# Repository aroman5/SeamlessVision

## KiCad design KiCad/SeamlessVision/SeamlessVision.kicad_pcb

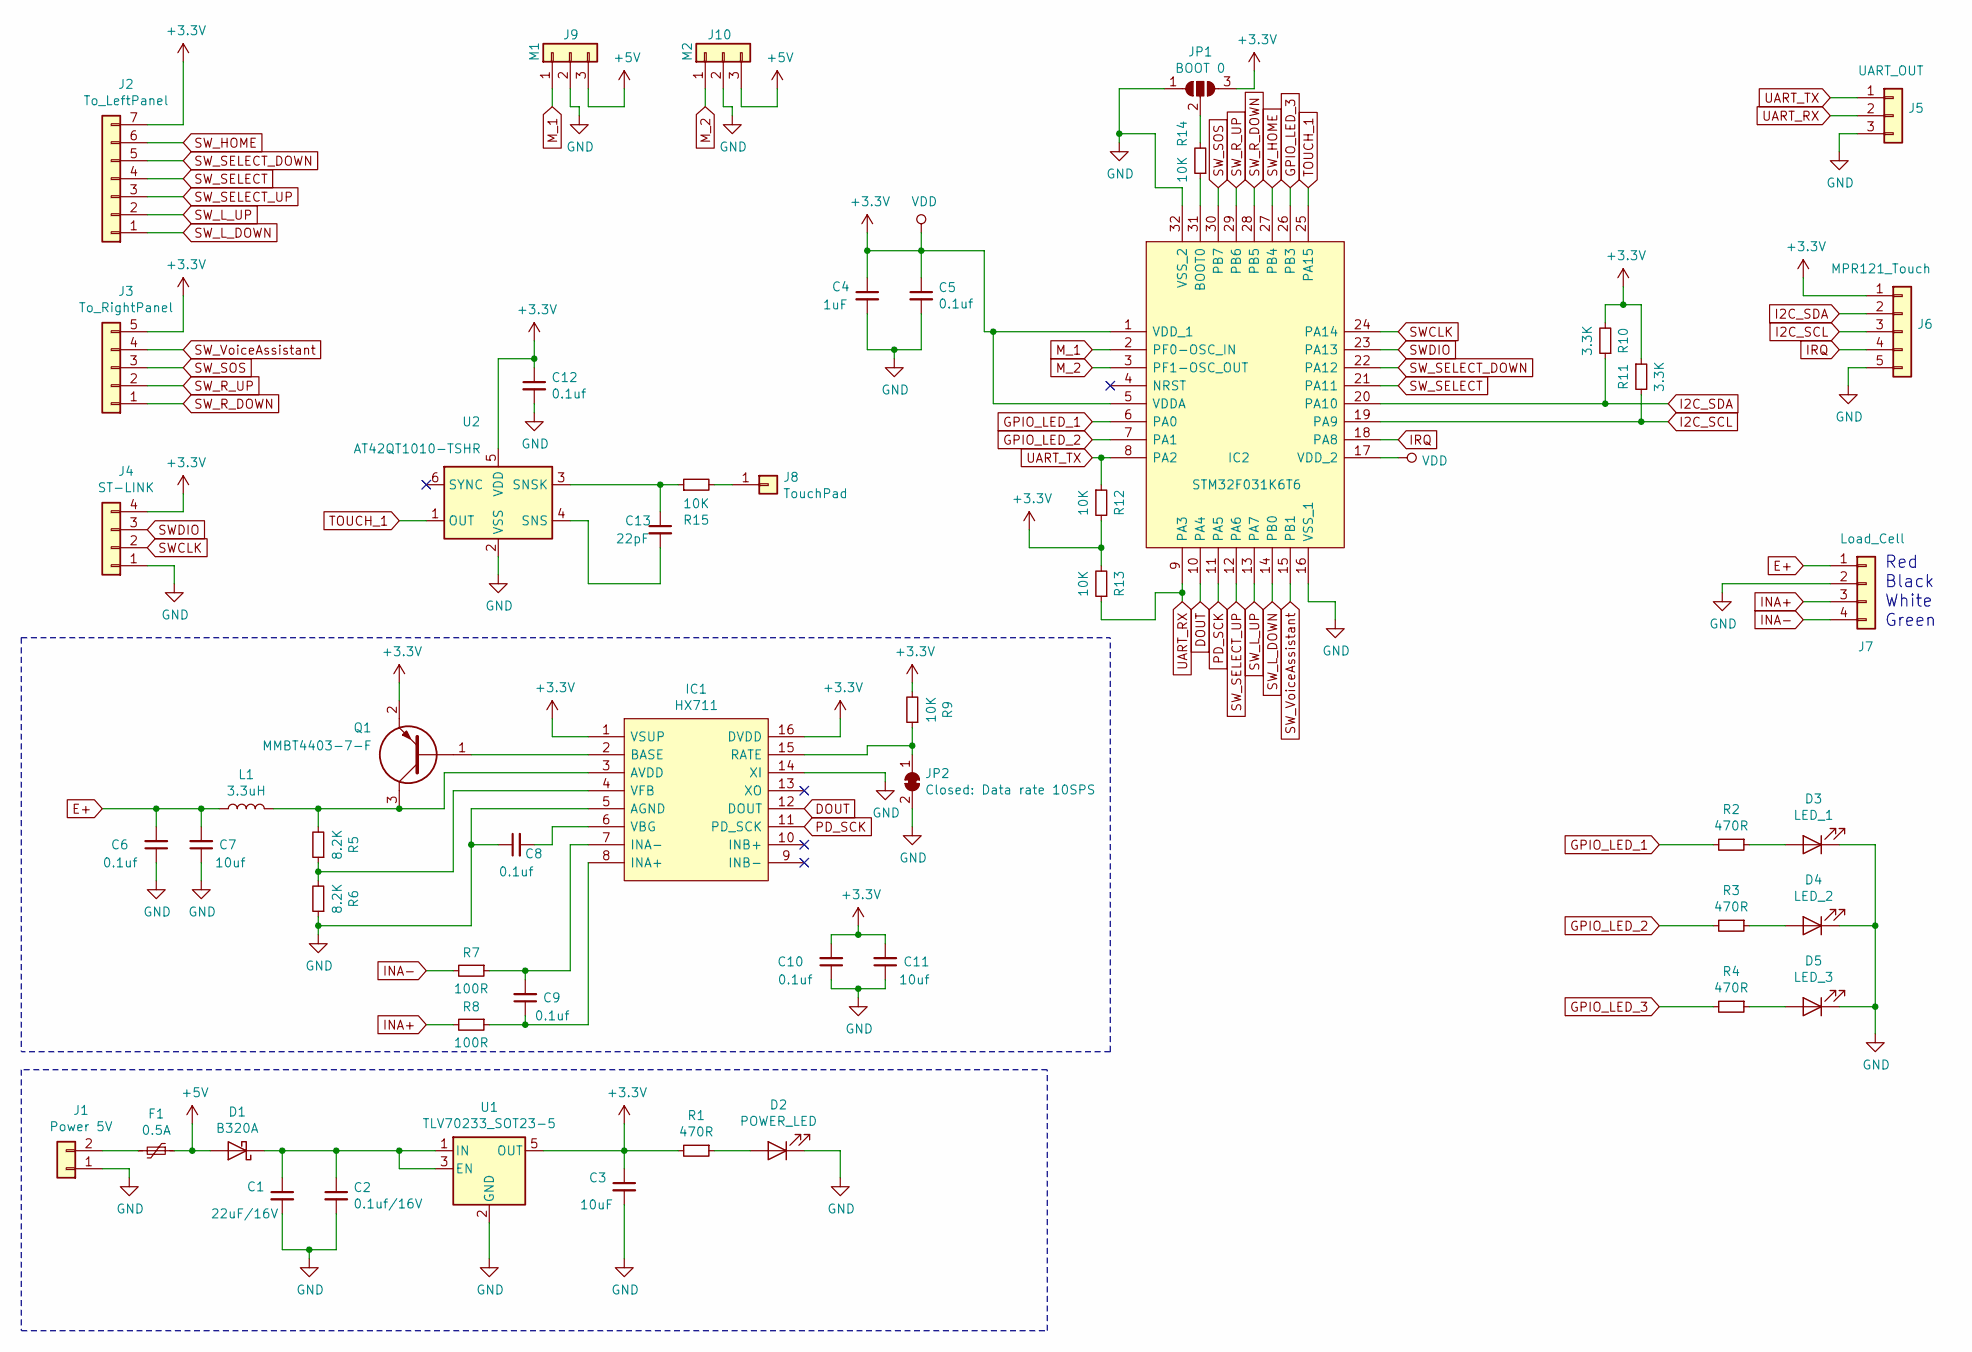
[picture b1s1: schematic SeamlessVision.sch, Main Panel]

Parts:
C1: 22uF/16V; C_1210_3225Metric
C2: 0.1uf/16V; C_0805_2012Metric
C3: 10uF; C_0805_2012Metric
C4: 1uF; C_0805_2012Metric
C5, C6, C8, C9, C10, C12: 0.1uf; C_0805_2012Metric
C7, C11: 10uf; C_0805_2012Metric
C13: 22pF; C_0805_2012Metric
D1: B320A; D_SMA
D2: POWER_LED; LED_0603_1608Metric
D3: LED_1; LED_0603_1608Metric
D4: LED_2; LED_0603_1608Metric
D5: LED_3; LED_0603_1608Metric
F1: 0.5A; FUSC3216X55N
IC1: HX711; SOIC127P600X160-16N; Manufacturer_Part_Number HX711
IC2: STM32F031K6T6; QFP80P900X900X160-32N; Mouser Part Number 511-STM32F031K6T6
J1: Power 5V; JST_PH_B2B-PH-SM4-TB_02x2.00mm_Straight
J2: To_LeftPanel; Molex_PicoBlade_53261-0771_1x07-1MP_P1.25mm_Horizontal
J3: To_RightPanel; Molex_PicoBlade_53261-0571_1x05-1MP_P1.25mm_Horizontal
J4: ST-LINK; Molex_PicoBlade_53398-0471_1x04-1MP_P1.25mm_Vertical
J5: UART_OUT; Molex_PicoBlade_53261-0371_1x03-1MP_P1.25mm_Horizontal
J6: MPR121_Touch; Molex_PicoBlade_53261-0571_1x05-1MP_P1.25mm_Horizontal
J7: Load_Cell; Molex_PicoBlade_53398-0471_1x04-1MP_P1.25mm_Vertical
J8: TouchPad; PinHeader_1x01_P2.54mm_Vertical
J9: M1; Molex_PicoBlade_53398-0371_1x03-1MP_P1.25mm_Vertical
J10: M2; Molex_PicoBlade_53398-0371_1x03-1MP_P1.25mm_Vertical
JP1: BOOT 0; SolderJumper-3_P1.3mm_Open_RoundedPad1.0x1.5mm
JP2: Closed: Data rate 10SPS; SolderJumper-2_P1.3mm_Bridged_RoundedPad1.0x1.5mm
L1: 3.3uH; L_1210
Q1: MMBT4403-7-F; SOT96P240X120-3N; Mouser Part Number 621-MMBT4403-F
R1, R2, R3, R4: 470R; R_0603_1608Metric
R5, R6: 8.2K; R_0603_1608Metric
R7, R8: 100R; R_0603_1608Metric
R9, R12, R13, R14, R15: 10K; R_0603_1608Metric
R10, R11: 3.3K; R_0603_1608Metric
U1: TLV70233_SOT23-5; SOT-23-5
U2: AT42QT1010-TSHR; SOT-23-6

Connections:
+3V3: C3.1, C4.1, C5.1, C10.2, C11.2, C12.1, IC1.1 (VSUP), IC1.16 (DVDD), IC2.1 (VDD_1), IC2.5 (VDDA), IC2.17 (VDD_2), J2.7, J3.5, J4.4, J6.1, JP1.3 (B), Q1.2, R1.2, R9.2, R10.2, R11.1, R12.2, R13.2, U1.5 (OUT), U2.5 (VDD); also elsewhere on the board
+5V: D1.2 (A), F1.1, J9.3, J10.3
DOUT: IC1.12 (DOUT), IC2.10 (PA4)
E+: C6.2, C7.2, J7.1, L1.1
GND: C1.2, C2.2, C3.2, C4.2, C5.2, C6.1, C7.1, C8.1, C10.1, C11.1, C12.2, D2.1 (K), D3.1 (K), D4.1 (K), D5.1 (K), IC1.5 (AGND), IC1.14 (XI), IC2.16 (VSS_1), IC2.32 (VSS_2), J1.1, J4.1, J5.3, J6.5, J7.2, J9.2, J10.2, JP1.1 (A), JP2.2 (B), R6.1, U1.2 (GND), U2.2 (VSS); also elsewhere on the board
GPIO_LED_1: IC2.6 (PA0), R2.2
GPIO_LED_2: IC2.7 (PA1), R3.2
GPIO_LED_3: IC2.26 (PB3), R4.2
I2C_SCL: IC2.19 (PA9), J6.3, R11.2
I2C_SDA: IC2.20 (PA10), J6.2, R10.1
INA+: J7.3, R8.2
INA-: J7.4, R7.2
IRQ: IC2.18 (PA8), J6.4
M_1: IC2.2 (PF0-OSC_IN), J9.1
M_2: IC2.3 (PF1-OSC_OUT), J10.1
unnamed: C1.1, C2.1, D1.1 (K), U1.1 (IN), U1.3 (EN)
unnamed: C8.2, IC1.6 (VBG)
unnamed: C9.1, IC1.8 (INA+), R8.1
unnamed: C9.2, IC1.7 (INA-), R7.1
unnamed: C13.1, R15.1, U2.3 (SNSK)
unnamed: C13.2, U2.4 (SNS)
unnamed: D2.2 (A), R1.1
unnamed: D3.2 (A), R2.1
unnamed: D4.2 (A), R3.1
unnamed: D5.2 (A), R4.1
unnamed: F1.2, J1.2
unnamed: IC1.2 (BASE), Q1.1
unnamed: IC1.3 (AVDD), L1.2, Q1.3, R5.2
unnamed: IC1.4 (VFB), R5.1, R6.2
unnamed: IC1.15 (RATE), JP2.1 (A), R9.1
unnamed: IC2.31 (BOOT0), R14.1
unnamed: J8.1, R15.2
unnamed 32: JP1.2 (C), R14.2; also elsewhere on the board
PD_SCK: IC1.11 (PD_SCK), IC2.11 (PA5)
SWCLK: IC2.24 (PA14), J4.2
SWDIO: IC2.23 (PA13), J4.3
SW_HOME: IC2.27 (PB4), J2.6
SW_L_DOWN: IC2.14 (PB0), J2.1
SW_L_UP: IC2.13 (PA7), J2.2
SW_R_DOWN: IC2.28 (PB5), J3.1
SW_R_UP: IC2.29 (PB6), J3.2
SW_SELECT: IC2.21 (PA11), J2.4
SW_SELECT_DOWN: IC2.22 (PA12), J2.5
SW_SELECT_UP: IC2.12 (PA6), J2.3
SW_SOS: IC2.30 (PB7), J3.3
SW_VoiceAssistant: IC2.15 (PB1), J3.4
TOUCH_1: IC2.25 (PA15), U2.1 (OUT)
UART_RX: IC2.9 (PA3), J5.2, R13.1
UART_TX: IC2.8 (PA2), J5.1, R12.1

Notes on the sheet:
Red Black White Green

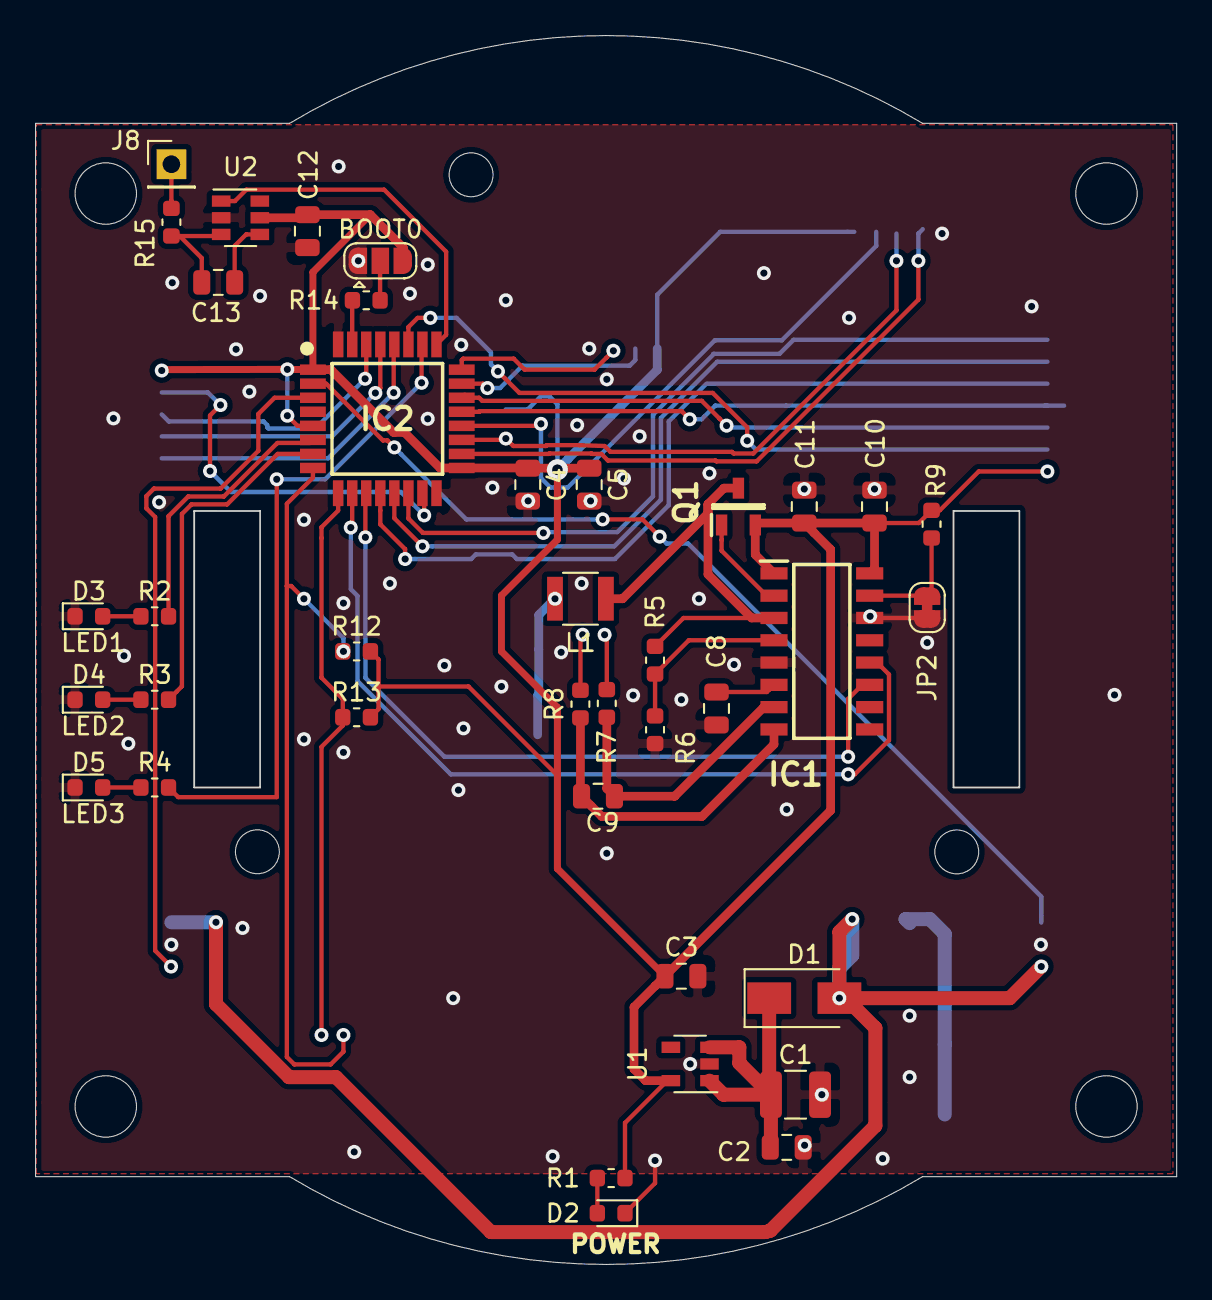
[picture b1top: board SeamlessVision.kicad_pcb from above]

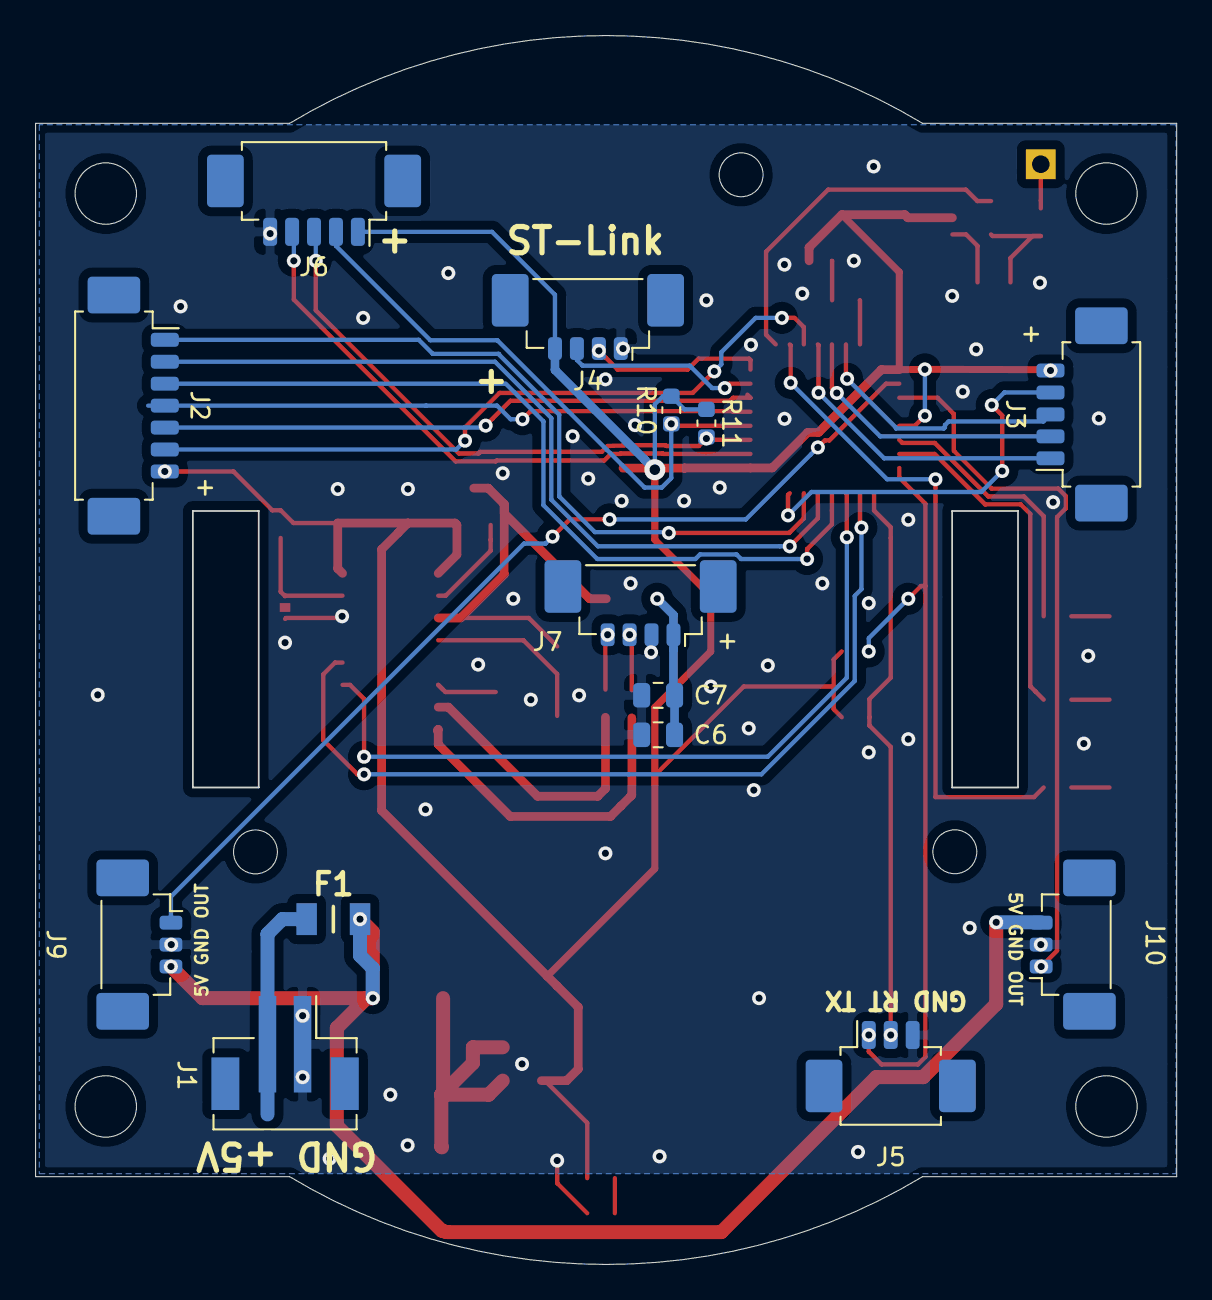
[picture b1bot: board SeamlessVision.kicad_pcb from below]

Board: 2 copper layers, 65.0 x 70.0 mm, 52 parts (14 on the bottom side), 49 nets.

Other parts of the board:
BOOT0: BOOT 0; SolderJumper-3_P1.3mm_Open_RoundedPad1.0x1.5mm

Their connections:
+3V3: BOOT0.3; also elsewhere on the board
GND: BOOT0.1; also elsewhere on the board
unnamed 32: BOOT0.2; also elsewhere on the board

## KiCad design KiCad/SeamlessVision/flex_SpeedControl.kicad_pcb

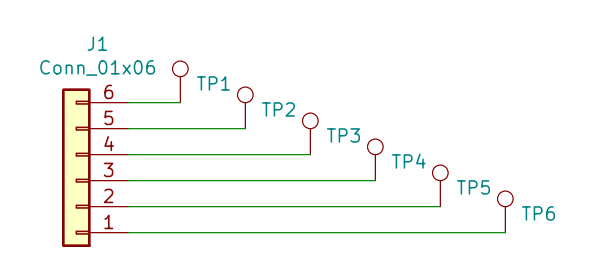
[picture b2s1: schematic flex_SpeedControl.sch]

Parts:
J1: Conn_01x06; PinHeader_2x03_P2.00mm_Vertical_SMD
TP1, TP2, TP3, TP4, TP5, TP6: TestPoint; TestPoint_Pad_D1.0mm

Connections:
unnamed: J1.1, TP6.1
unnamed: J1.2, TP5.1
unnamed: J1.3, TP4.1
unnamed: J1.4, TP3.1
unnamed: J1.5, TP2.1
unnamed: J1.6, TP1.1

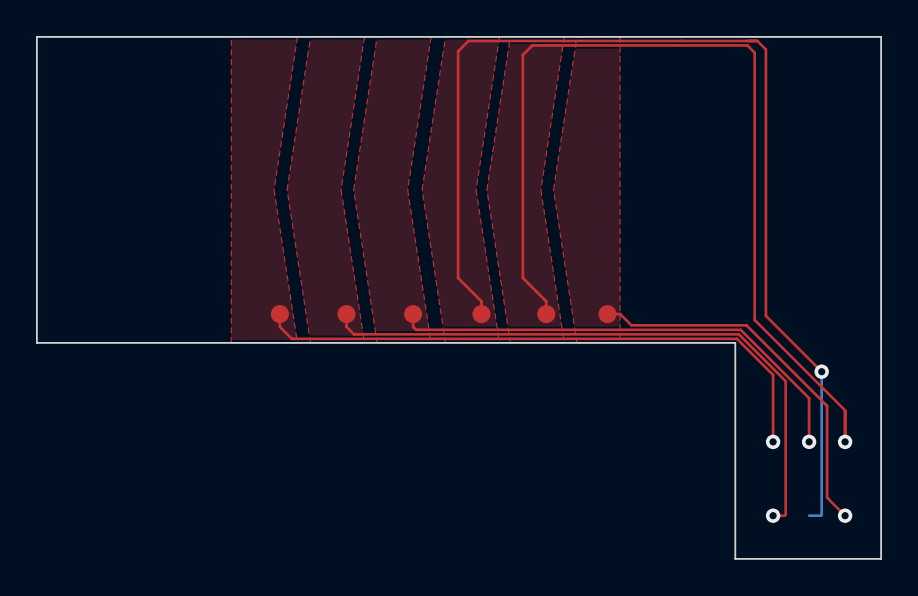
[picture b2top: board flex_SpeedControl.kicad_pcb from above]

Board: 2 copper layers, 46.9 x 29.0 mm, 7 parts (1 on the bottom side), 6 nets.

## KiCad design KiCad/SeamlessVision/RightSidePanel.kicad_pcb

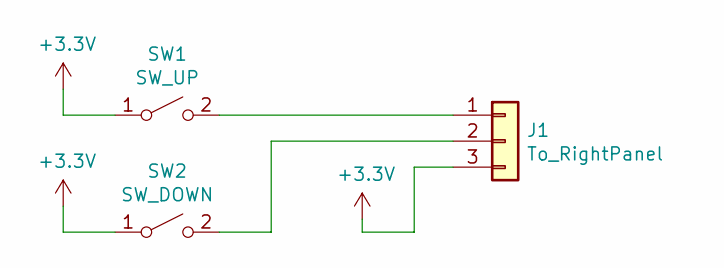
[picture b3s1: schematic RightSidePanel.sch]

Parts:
J1: To_RightPanel; Molex_PicoBlade_53398-0371_1x03-1MP_P1.25mm_Vertical
SW1: SW_UP; B3FS4002P
SW2: SW_DOWN; B3FS4002P

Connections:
+3V3: J1.3, SW1.1 (A), SW2.1 (A)
unnamed: J1.1, SW1.2 (B)
unnamed: J1.2, SW2.2 (B)

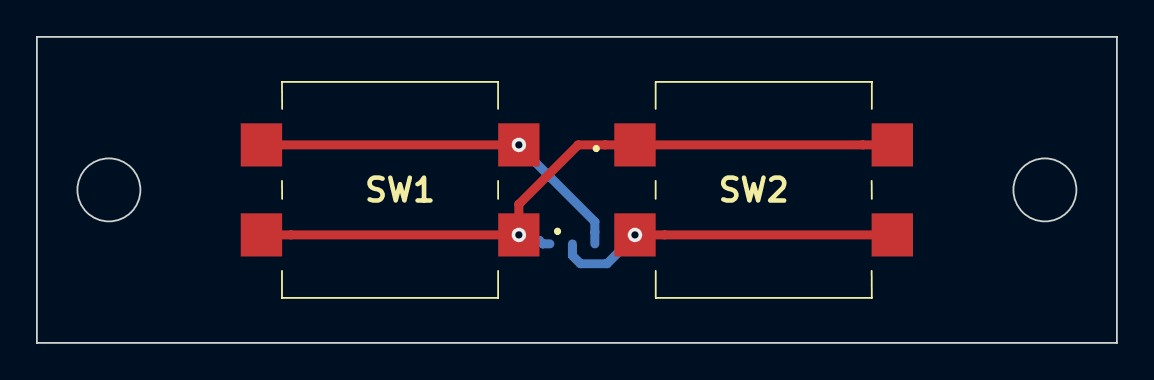
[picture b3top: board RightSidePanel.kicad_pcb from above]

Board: 2 copper layers, 60.0 x 17.0 mm, 3 parts (1 on the bottom side), 3 nets.

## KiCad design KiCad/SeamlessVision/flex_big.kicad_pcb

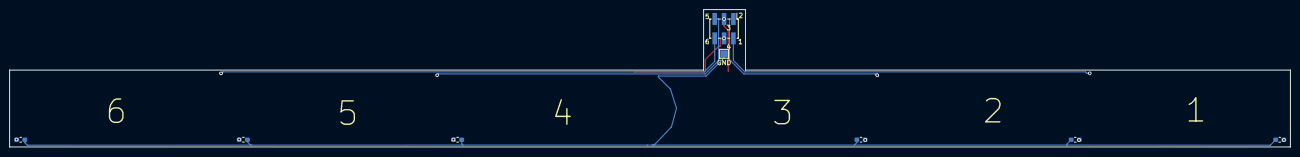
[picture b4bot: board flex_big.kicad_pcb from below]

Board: 2 copper layers, 275.0 x 29.5 mm, 8 parts (8 on the bottom side), 7 nets.

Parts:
C1, C2, C3, C4, C5, C6: 10pF; C_0603_1608Metric_Pad1.05x0.95mm_HandSolder
GND: Conn_01x07; TestPoint_Pad_1.5x1.5mm
J1: Conn_01x07; PinHeader_2x03_P2.00mm_Vertical_SMD

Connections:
GND: C1.2, C2.2, C3.2, C4.2, C5.2, C6.2, GND.1
unnamed: C1.1, J1.1
unnamed: C2.1, J1.2
unnamed: C3.1, J1.3
unnamed: C4.1, J1.4
unnamed: C5.1, J1.5
unnamed: C6.1, J1.6

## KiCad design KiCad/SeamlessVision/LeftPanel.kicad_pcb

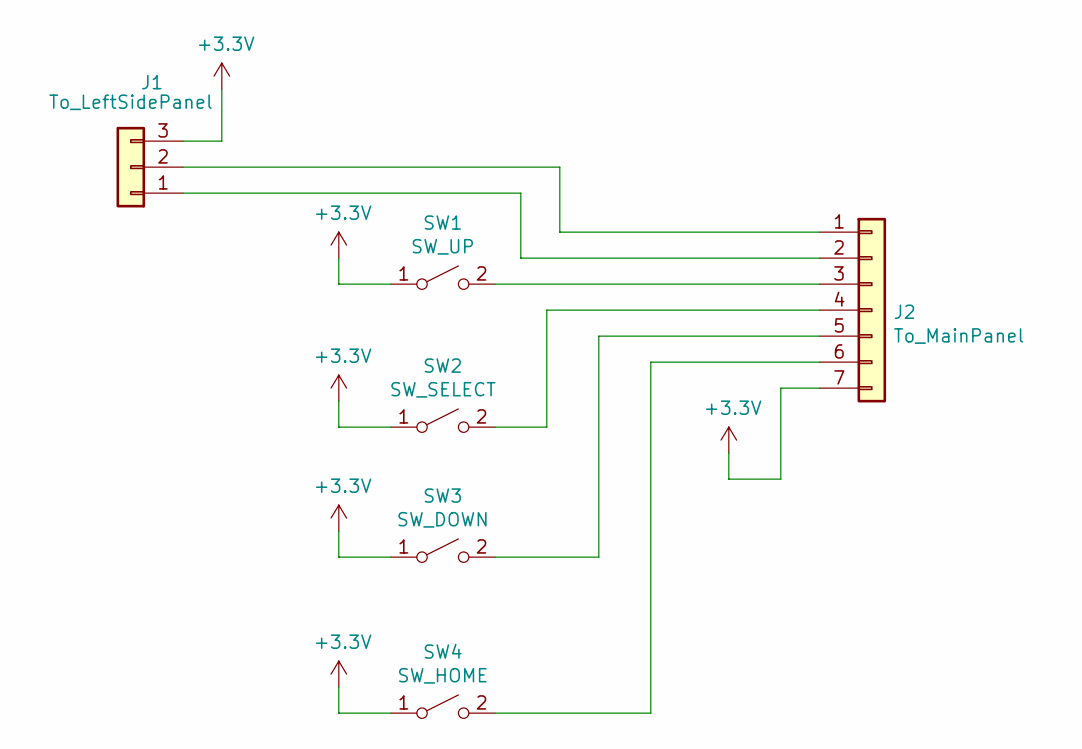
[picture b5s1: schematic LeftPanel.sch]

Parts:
J1: To_LeftSidePanel; Molex_PicoBlade_53261-0371_1x03-1MP_P1.25mm_Horizontal
J2: To_MainPanel; Molex_PicoBlade_53261-0771_1x07-1MP_P1.25mm_Horizontal
SW1: SW_UP; B3FS4002P
SW2: SW_SELECT; B3FS4002P
SW3: SW_DOWN; B3FS4002P
SW4: SW_HOME; B3FS4002P

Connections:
+3V3: J1.3, J2.7, SW1.1 (A), SW2.1 (A), SW3.1 (A), SW4.1 (A)
unnamed: J1.1, J2.2
unnamed: J1.2, J2.1
unnamed: J2.3, SW1.2 (B)
unnamed: J2.4, SW2.2 (B)
unnamed: J2.5, SW3.2 (B)
unnamed: J2.6, SW4.2 (B)

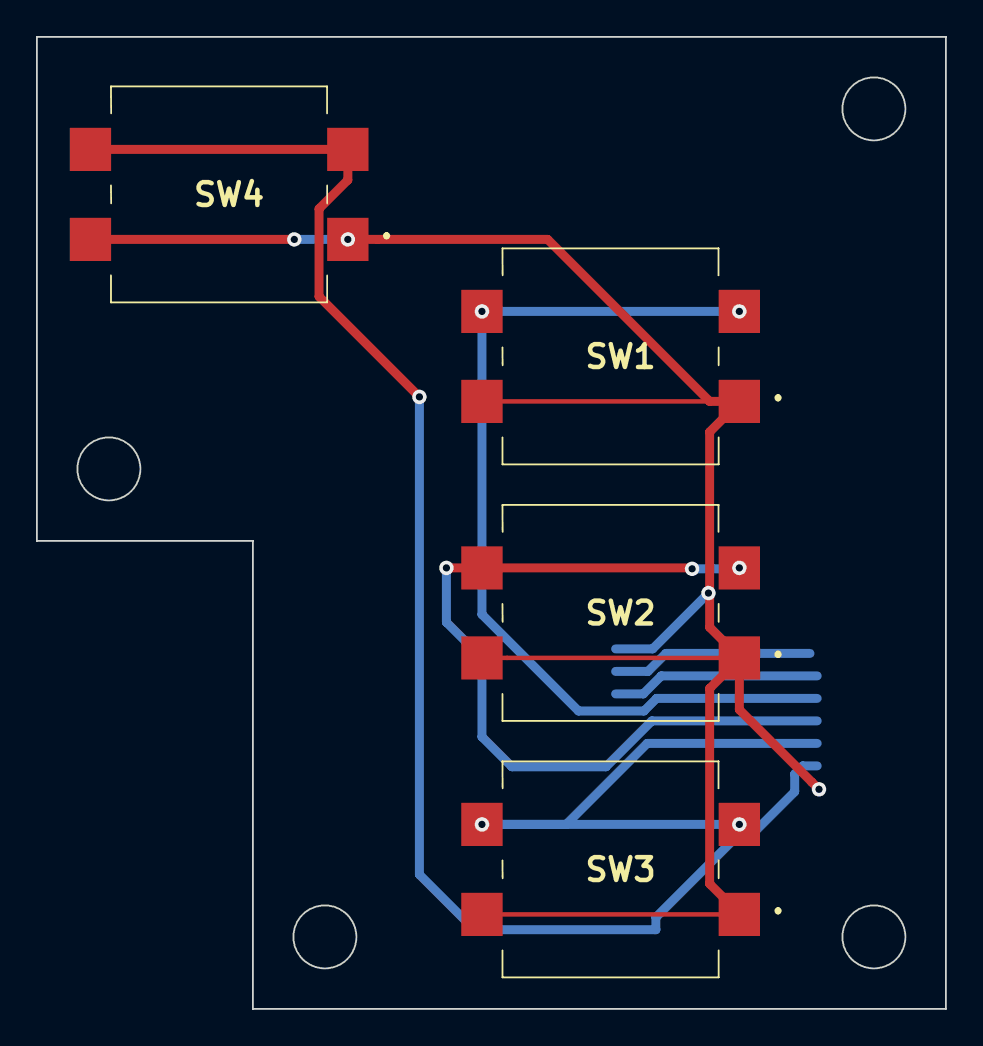
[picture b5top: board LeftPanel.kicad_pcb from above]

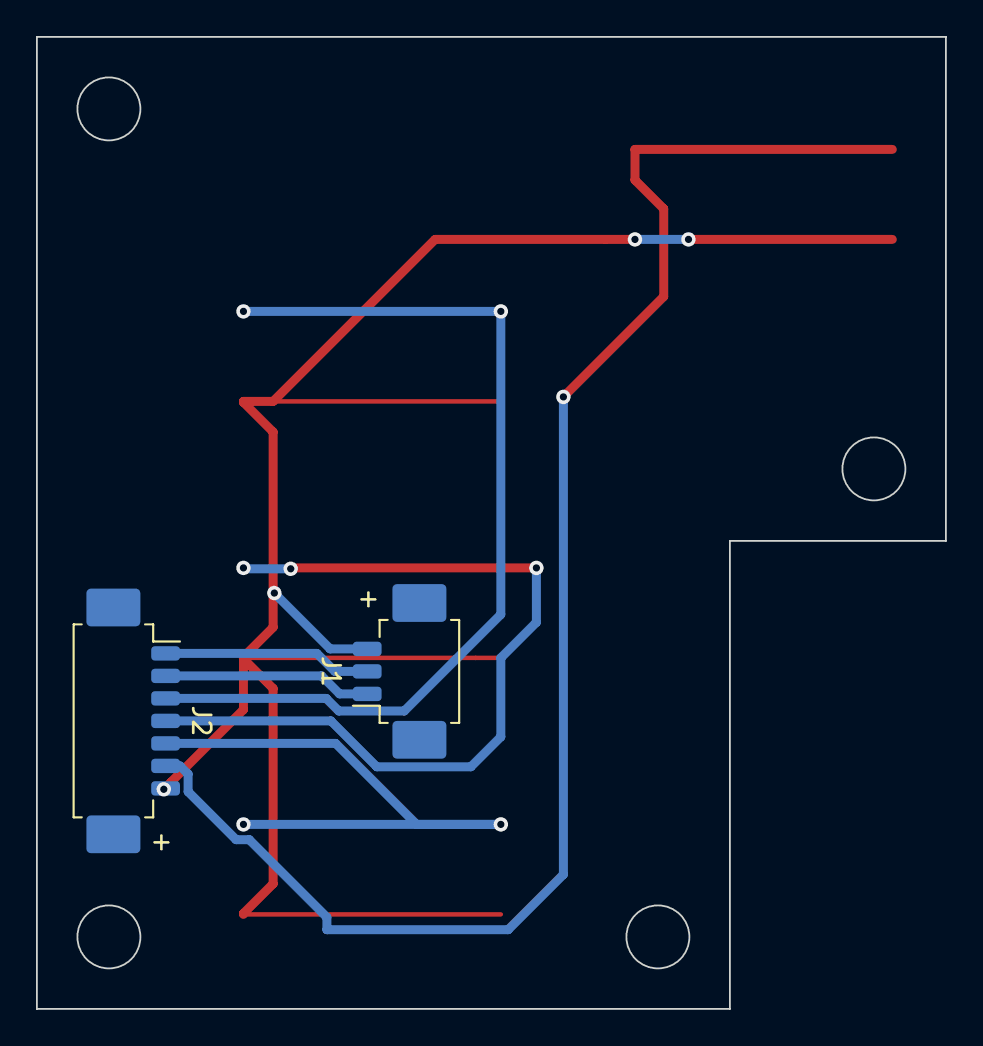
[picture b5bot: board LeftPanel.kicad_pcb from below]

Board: 2 copper layers, 50.5 x 54.0 mm, 6 parts (2 on the bottom side), 7 nets.

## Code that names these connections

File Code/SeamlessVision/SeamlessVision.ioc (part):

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Mcu.Name=STM32F031K6Tx
Mcu.Package=LQFP32
Mcu.UserName=STM32F031K6Tx
PA0.GPIOParameters=GPIO_Label
PA0.GPIO_Label=LED_1
PA0.Signal=GPIO_Output
PA1.GPIOParameters=GPIO_Label
PA1.GPIO_Label=LED_2
PA1.Signal=GPIO_Output
PA10.Mode=I2C
PA10.Signal=I2C1_SDA
PA11.GPIOParameters=GPIO_PuPd,GPIO_Label
PA11.GPIO_Label=SW_SELECT
PA11.GPIO_PuPd=GPIO_PULLDOWN
PA11.Signal=GPIO_Input
PA12.GPIOParameters=GPIO_PuPd,GPIO_Label
PA12.GPIO_Label=SW_SELECT_DOWN
PA12.GPIO_PuPd=GPIO_PULLDOWN
PA12.Signal=GPIO_Input
PA13.Mode=Serial_Wire
PA13.Signal=SYS_SWDIO
PA14.Mode=Serial_Wire
PA14.Signal=SYS_SWCLK
PA15.GPIOParameters=GPIO_PuPd,GPIO_Label
PA15.GPIO_Label=TOUCH_1
PA15.GPIO_PuPd=GPIO_NOPULL
PA15.Signal=GPIO_Input
PA2.Mode=Asynchronous
PA2.Signal=USART1_TX
PA3.Mode=Asynchronous
PA3.Signal=USART1_RX
PA4.GPIOParameters=GPIO_PuPd,GPIO_Label
PA4.GPIO_Label=HX711OUTPUT
PA4.GPIO_PuPd=GPIO_PULLDOWN
PA4.Signal=GPIO_Input
PA5.GPIOParameters=GPIO_PuPd,GPIO_Label
PA5.GPIO_Label=HX711SCK
PA5.GPIO_PuPd=GPIO_NOPULL
PA5.Signal=GPIO_Output
PA6.GPIOParameters=GPIO_PuPd,GPIO_Label
PA6.GPIO_Label=SW_SELECT_UP
PA6.GPIO_PuPd=GPIO_PULLDOWN
PA6.Signal=GPIO_Input
PA7.GPIOParameters=GPIO_PuPd,GPIO_Label
PA7.GPIO_Label=SW_L_UP
PA7.GPIO_PuPd=GPIO_PULLDOWN
PA7.Signal=GPIO_Input
PA8.GPIOParameters=GPIO_PuPd,GPIO_Label
PA8.GPIO_Label=IRQ
PA8.GPIO_PuPd=GPIO_PULLUP
PA8.Signal=GPXTI8
PA9.Mode=I2C
PA9.Signal=I2C1_SCL
PB0.GPIOParameters=GPIO_PuPd,GPIO_Label
PB0.GPIO_Label=SW_L_DOWN
PB0.GPIO_PuPd=GPIO_PULLDOWN
PB0.Signal=GPIO_Input
PB1.GPIOParameters=GPIO_PuPd,GPIO_Label
PB1.GPIO_Label=SW_VOICE
PB1.GPIO_PuPd=GPIO_PULLDOWN
PB1.Signal=GPIO_Input
PB3.GPIOParameters=GPIO_Label
PB3.GPIO_Label=LED_3
PB3.Signal=GPIO_Output
PB4.GPIOParameters=GPIO_PuPd,GPIO_Label
PB4.GPIO_Label=SW_HOME
PB4.GPIO_PuPd=GPIO_PULLDOWN
PB4.Signal=GPIO_Input
PB5.GPIOParameters=GPIO_PuPd,GPIO_Label
PB5.GPIO_Label=SW_R_DOWN
PB5.GPIO_PuPd=GPIO_PULLDOWN
PB5.Signal=GPIO_Input
PB6.GPIOParameters=GPIO_PuPd,GPIO_Label
PB6.GPIO_Label=SW_R_UP
PB6.GPIO_PuPd=GPIO_PULLDOWN
PB6.Signal=GPIO_Input
PB7.GPIOParameters=GPIO_PuPd,GPIO_Label
PB7.GPIO_Label=SW_SOS
PB7.GPIO_PuPd=GPIO_PULLDOWN
PB7.Signal=GPIO_Input
PF0-OSC_IN.GPIOParameters=GPIO_PuPd,GPIO_Label,GPIO_ModeDefaultOutputPP
PF0-OSC_IN.GPIO_Label=M_1
PF0-OSC_IN.GPIO_ModeDefaultOutputPP=GPIO_MODE_OUTPUT_PP
PF0-OSC_IN.GPIO_PuPd=GPIO_PULLDOWN
PF0-OSC_IN.Signal=GPIO_Output
PF1-OSC_OUT.GPIOParameters=PinState,GPIO_PuPd,GPIO_Label,GPIO_ModeDefaultOutputPP
PF1-OSC_OUT.GPIO_Label=M_2
PF1-OSC_OUT.GPIO_ModeDefaultOutputPP=GPIO_MODE_OUTPUT_PP
PF1-OSC_OUT.GPIO_PuPd=GPIO_PULLDOWN
PF1-OSC_OUT.PinState=GPIO_PIN_RESET
PF1-OSC_OUT.Signal=GPIO_Output
RCC.SYSCLKFreq_VALUE=48000000
RCC.SYSCLKSource=RCC_SYSCLKSOURCE_PLLCLK
board=custom

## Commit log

2020-04-28 Add files
